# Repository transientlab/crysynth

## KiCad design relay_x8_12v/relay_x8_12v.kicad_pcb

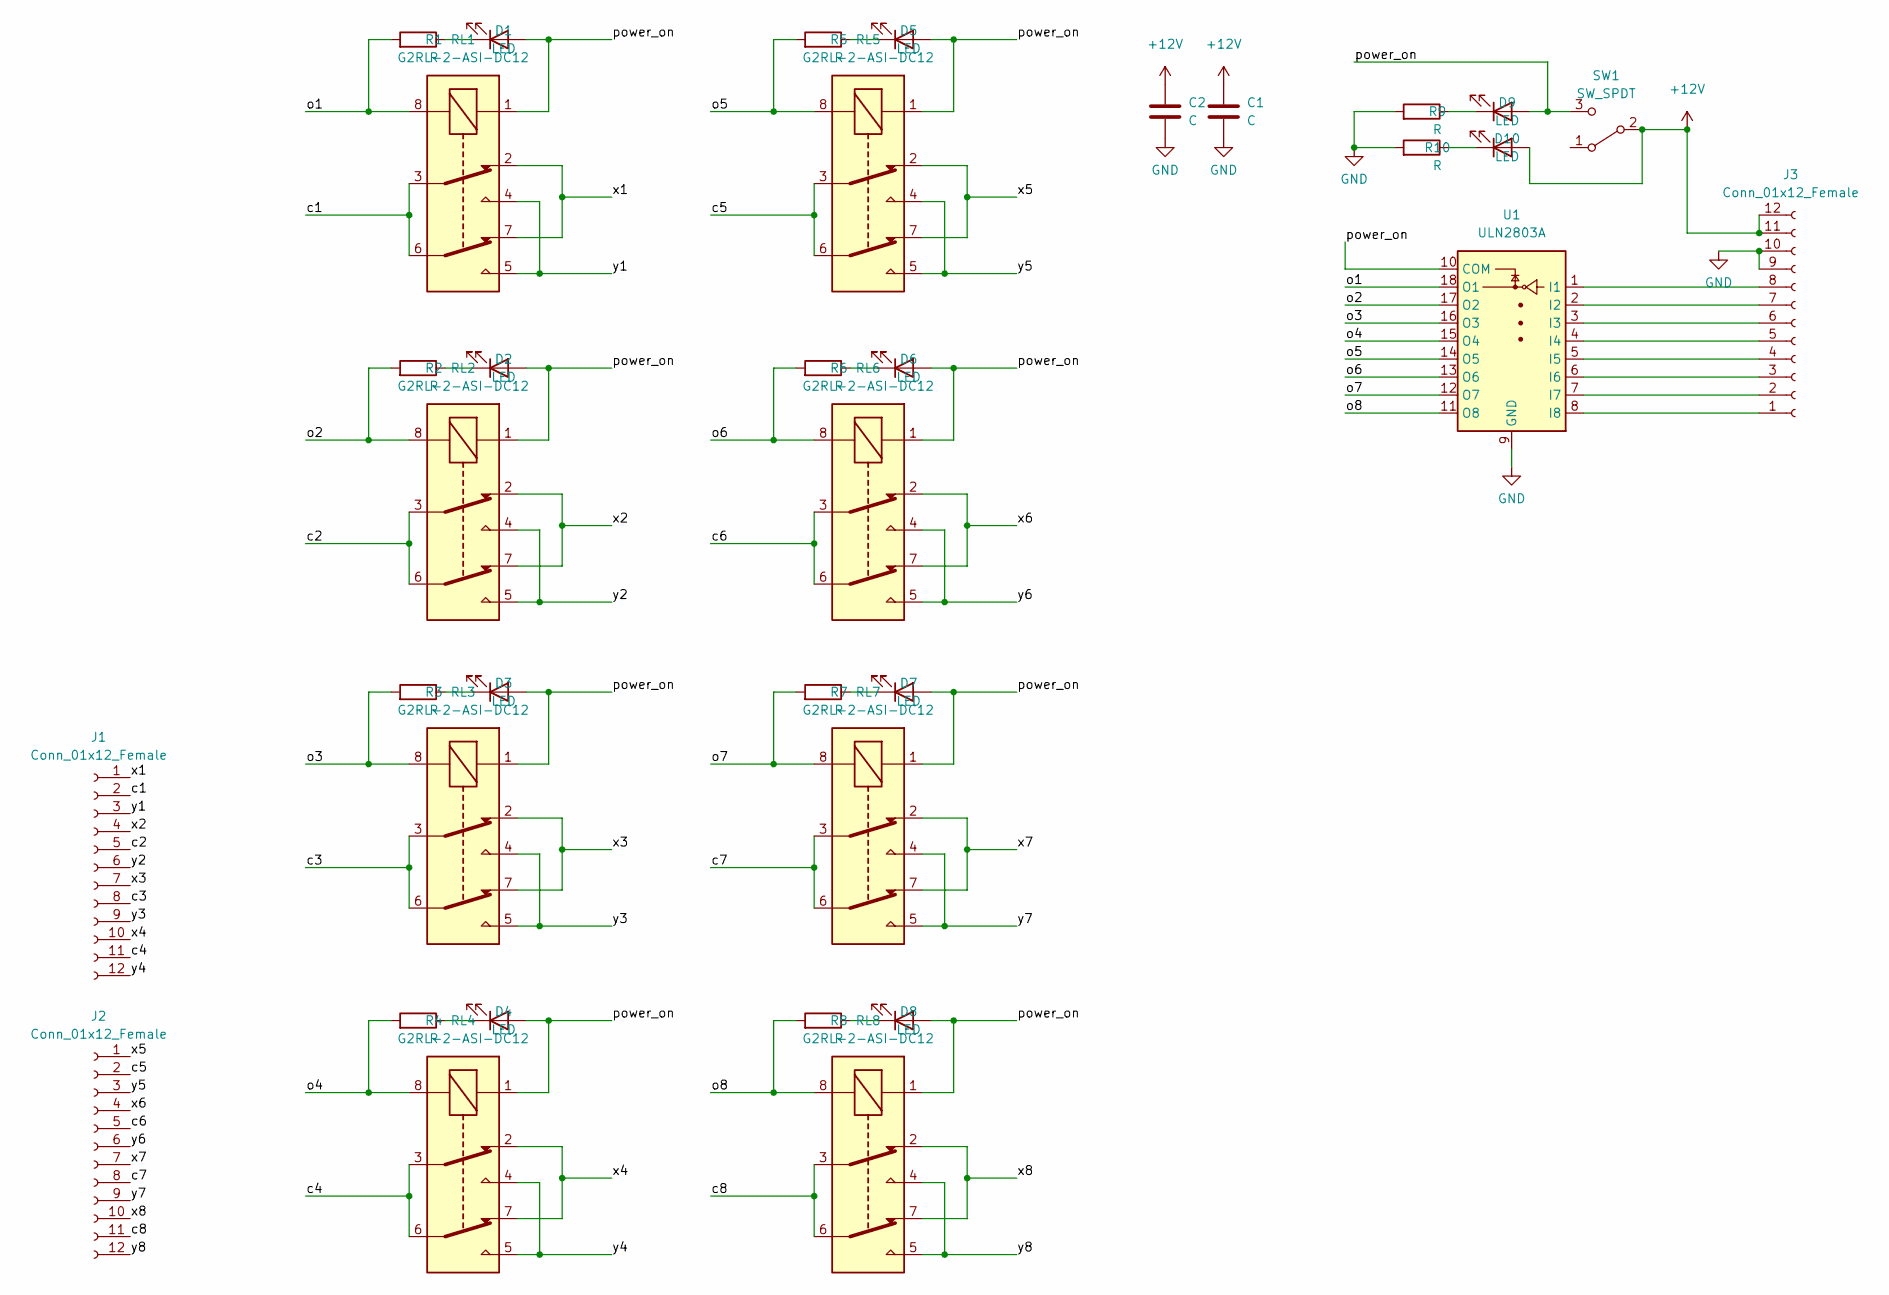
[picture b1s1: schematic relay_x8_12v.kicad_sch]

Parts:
C1, C2: C; C_Radial_D6.3mm_H11.0mm_P2.50mm
D1, D2, D3, D4, D5, D6, D7, D8, D9, D10: LED; LED_Rectangular_W5.0mm_H2.0mm
J1, J2, J3: Conn_01x12_Female; conn_large_12
R1, R2, R3, R4, R5, R6, R7, R8, R9, R10: R; R_Axial_DIN0207_L6.3mm_D2.5mm_P7.62mm_Horizontal
RL1, RL2, RL3, RL4, RL5, RL6, RL7, RL8: G2RL-2-ASI-DC12; Relay_DPDT_Omron_G2RL
SW1: SW_SPDT; sw_spdt_large
U1: ULN2803A; DIP-18_W7.62mm_Socket_LongPads

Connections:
+12V: C1.1, C2.1, D10.2 (A), J3.11, J3.12, SW1.2 (B)
/c1: J1.2, RL1.3, RL1.6
/c2: J1.5, RL2.3, RL2.6
/c3: J1.8, RL3.3, RL3.6
/c4: J1.11, RL4.3, RL4.6
/c5: J2.2, RL5.3, RL5.6
/c6: J2.5, RL6.3, RL6.6
/c7: J2.8, RL7.3, RL7.6
/c8: J2.11, RL8.3, RL8.6
/o1: R1.2, RL1.8, U1.18 (O1)
/o2: R2.2, RL2.8, U1.17 (O2)
/o3: R3.2, RL3.8, U1.16 (O3)
/o4: R4.2, RL4.8, U1.15 (O4)
/o5: R5.2, RL5.8, U1.14 (O5)
/o6: R6.2, RL6.8, U1.13 (O6)
/o7: R7.2, RL7.8, U1.12 (O7)
/o8: R8.2, RL8.8, U1.11 (O8)
/power_on: D1.2 (A), D2.2 (A), D3.2 (A), D4.2 (A), D5.2 (A), D6.2 (A), D7.2 (A), D8.2 (A), D9.2 (A), RL1.1, RL2.1, RL3.1, RL4.1, RL5.1, RL6.1, RL7.1, RL8.1, SW1.3 (C), U1.10 (COM)
/x1: J1.1, RL1.2, RL1.7
/x2: J1.4, RL2.2, RL2.7
/x3: J1.7, RL3.2, RL3.7
/x4: J1.10, RL4.2, RL4.7
/x5: J2.1, RL5.2, RL5.7
/x6: J2.4, RL6.2, RL6.7
/x7: J2.7, RL7.2, RL7.7
/x8: J2.10, RL8.2, RL8.7
/y1: J1.3, RL1.4, RL1.5
/y2: J1.6, RL2.4, RL2.5
/y3: J1.9, RL3.4, RL3.5
/y4: J1.12, RL4.4, RL4.5
/y5: J2.3, RL5.4, RL5.5
/y6: J2.6, RL6.4, RL6.5
/y7: J2.9, RL7.4, RL7.5
/y8: J2.12, RL8.4, RL8.5
GND: C1.2, C2.2, J3.9, J3.10, R9.2, R10.2, U1.9 (GND)
unnamed: D1.1 (K), R1.1
unnamed: D2.1 (K), R2.1
unnamed: D3.1 (K), R3.1
unnamed: D4.1 (K), R4.1
unnamed: D5.1 (K), R5.1
unnamed: D6.1 (K), R6.1
unnamed: D7.1 (K), R7.1
unnamed: D8.1 (K), R8.1
unnamed: D9.1 (K), R9.1
unnamed: D10.1 (K), R10.1
unnamed: J3.1, U1.8 (I8)
unnamed: J3.2, U1.7 (I7)
unnamed: J3.3, U1.6 (I6)
unnamed: J3.4, U1.5 (I5)
unnamed: J3.5, U1.4 (I4)
unnamed: J3.6, U1.3 (I3)
unnamed: J3.7, U1.2 (I2)
unnamed: J3.8, U1.1 (I1)

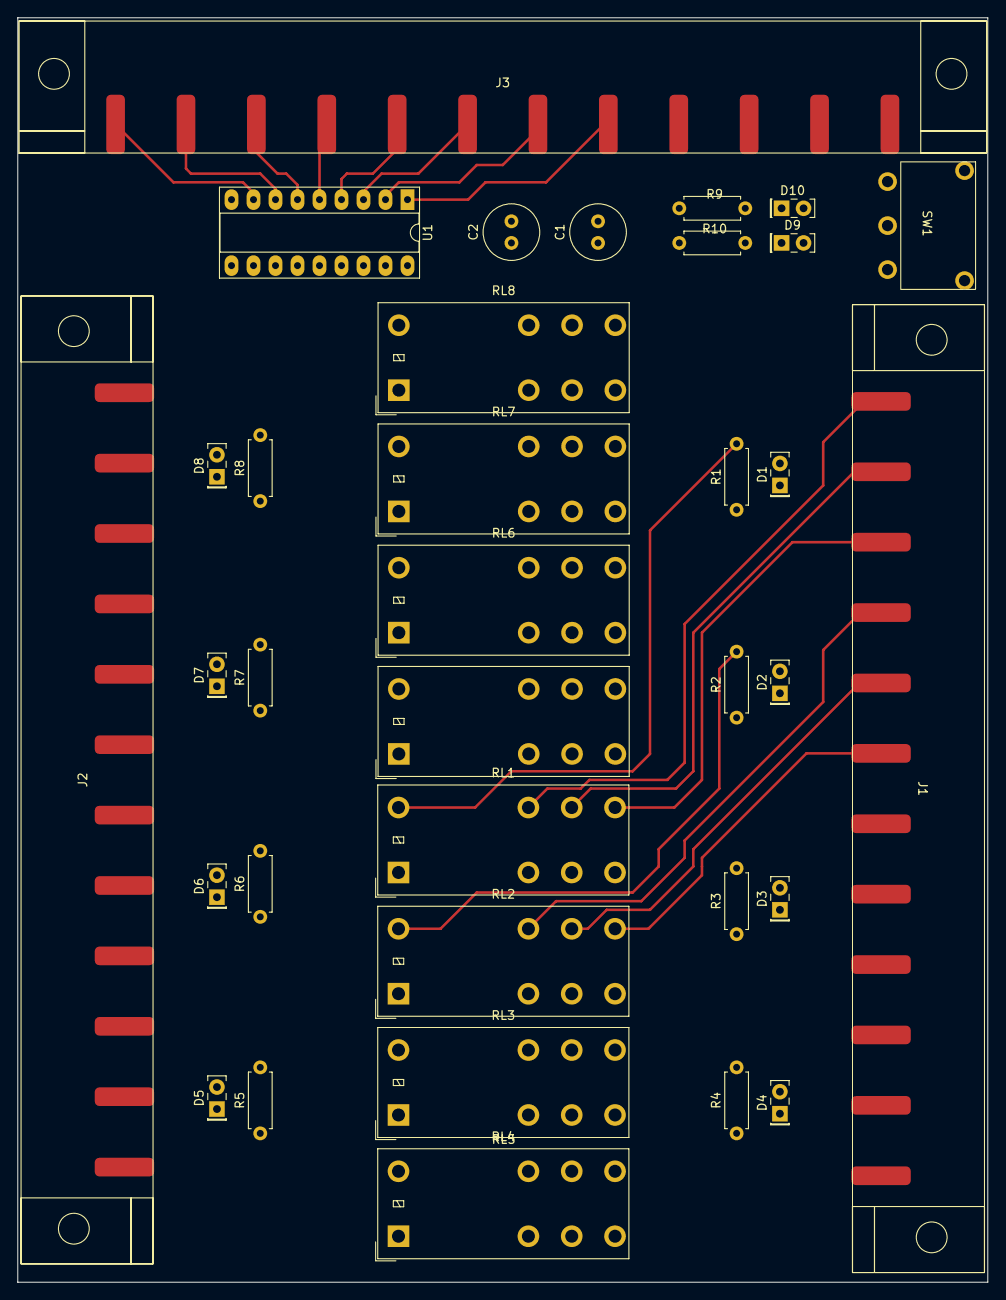
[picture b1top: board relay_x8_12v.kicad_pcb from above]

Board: 2 copper layers, 112.0 x 146.0 mm, 35 parts (0 on the bottom side), 53 nets.

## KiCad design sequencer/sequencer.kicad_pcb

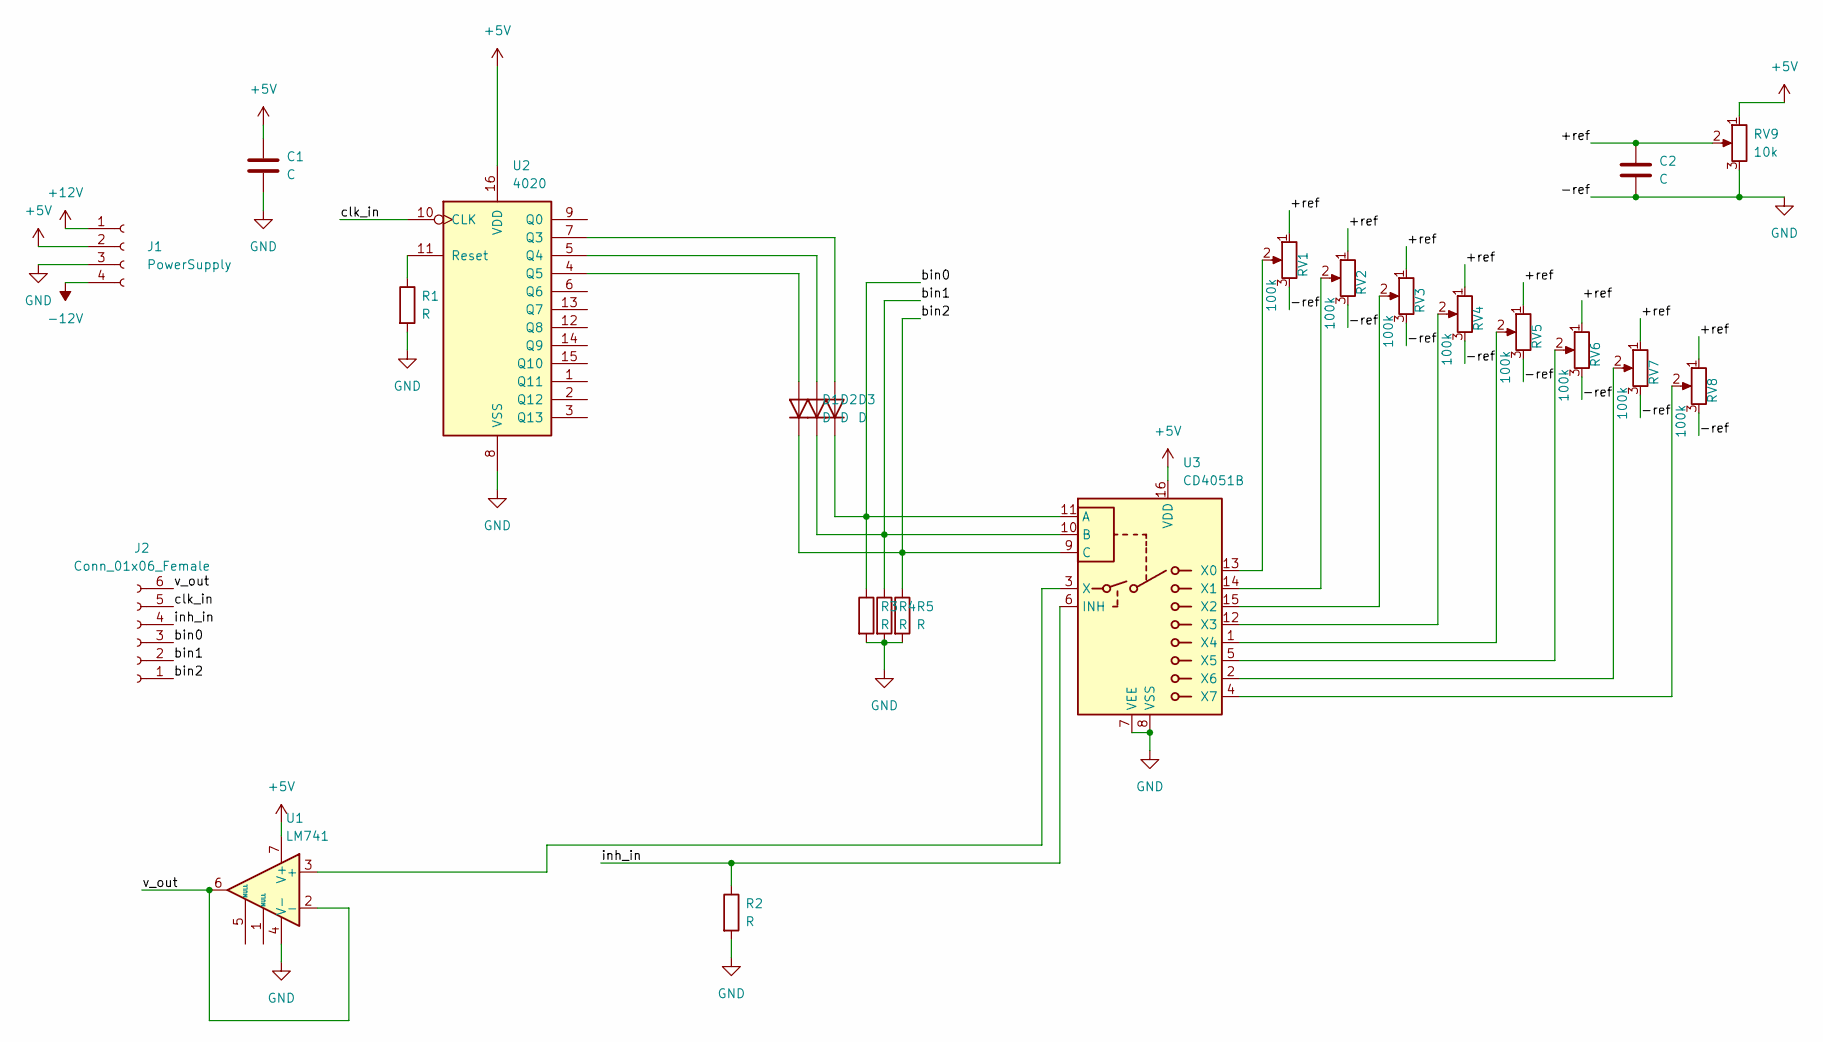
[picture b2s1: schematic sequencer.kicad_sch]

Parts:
C1, C2: C; C_Radial_D6.3mm_H11.0mm_P2.50mm
D1, D2, D3: D; D_T-1_P10.16mm_Horizontal
J1: PowerSupply; PinSocket_1x04_P1.27mm_Vertical
J2: Conn_01x06_Female; PinSocket_1x06_P2.54mm_Horizontal
R1, R2, R3, R4, R5: R; R_Axial_DIN0207_L6.3mm_D2.5mm_P7.62mm_Horizontal
RV1, RV2, RV3, RV4, RV5, RV6, RV7, RV8: 100k; Potentiometer_Alps_RK163_Single_Horizontal
RV9: 10k; Potentiometer_Alps_RK163_Single_Horizontal
U1: LM741; DIP-8_W7.62mm_Socket_LongPads
U2: 4020; DIP-16_W10.16mm_LongPads
U3: CD4051B; DIP-16_W7.62mm_Socket_LongPads

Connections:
+5V: C1.1, J1.2, RV9.1, U1.7 (V+), U2.16 (VDD), U3.16 (VDD)
+12V: J1.1
-12V: J1.4
/+ref: C2.1, RV1.1, RV2.1, RV3.1, RV4.1, RV5.1, RV6.1, RV7.1, RV8.1, RV9.2
/bin0: D3.1 (K), J2.3, R3.1, U3.11 (A)
/bin1: D2.1 (K), J2.2, R4.1, U3.10 (B)
/bin2: D1.1 (K), J2.1, R5.1, U3.9 (C)
/clk_in: J2.5, U2.10 (CLK)
/inh_in: J2.4, R2.1, U3.6 (INH)
/v_out: J2.6, U1.2 (-), U1.6
GND: C1.2, C2.2, J1.3, R1.2, R2.2, R3.2, R4.2, R5.2, RV1.3, RV2.3, RV3.3, RV4.3, RV5.3, RV6.3, RV7.3, RV8.3, RV9.3, U1.4 (V-), U2.8 (VSS), U3.7 (VEE), U3.8 (VSS)
unnamed: R1.1, U2.11 (Reset)
unnamed: RV1.2, U3.13 (X0)
unnamed: RV2.2, U3.14 (X1)
unnamed: RV3.2, U3.15 (X2)
unnamed: RV4.2, U3.12 (X3)
unnamed: RV5.2, U3.1 (X4)
unnamed: RV6.2, U3.5 (X5)
unnamed: RV7.2, U3.2 (X6)
unnamed: RV8.2, U3.4 (X7)
unnamed: U1.3 (+), U3.3 (X)
unnamed: D1.2 (A), U2.4 (Q5)
unnamed: D2.2 (A), U2.5 (Q4)
unnamed: D3.2 (A), U2.7 (Q3)

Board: 2 copper layers, 24 parts (0 on the bottom side), 22 nets, no tracks yet.

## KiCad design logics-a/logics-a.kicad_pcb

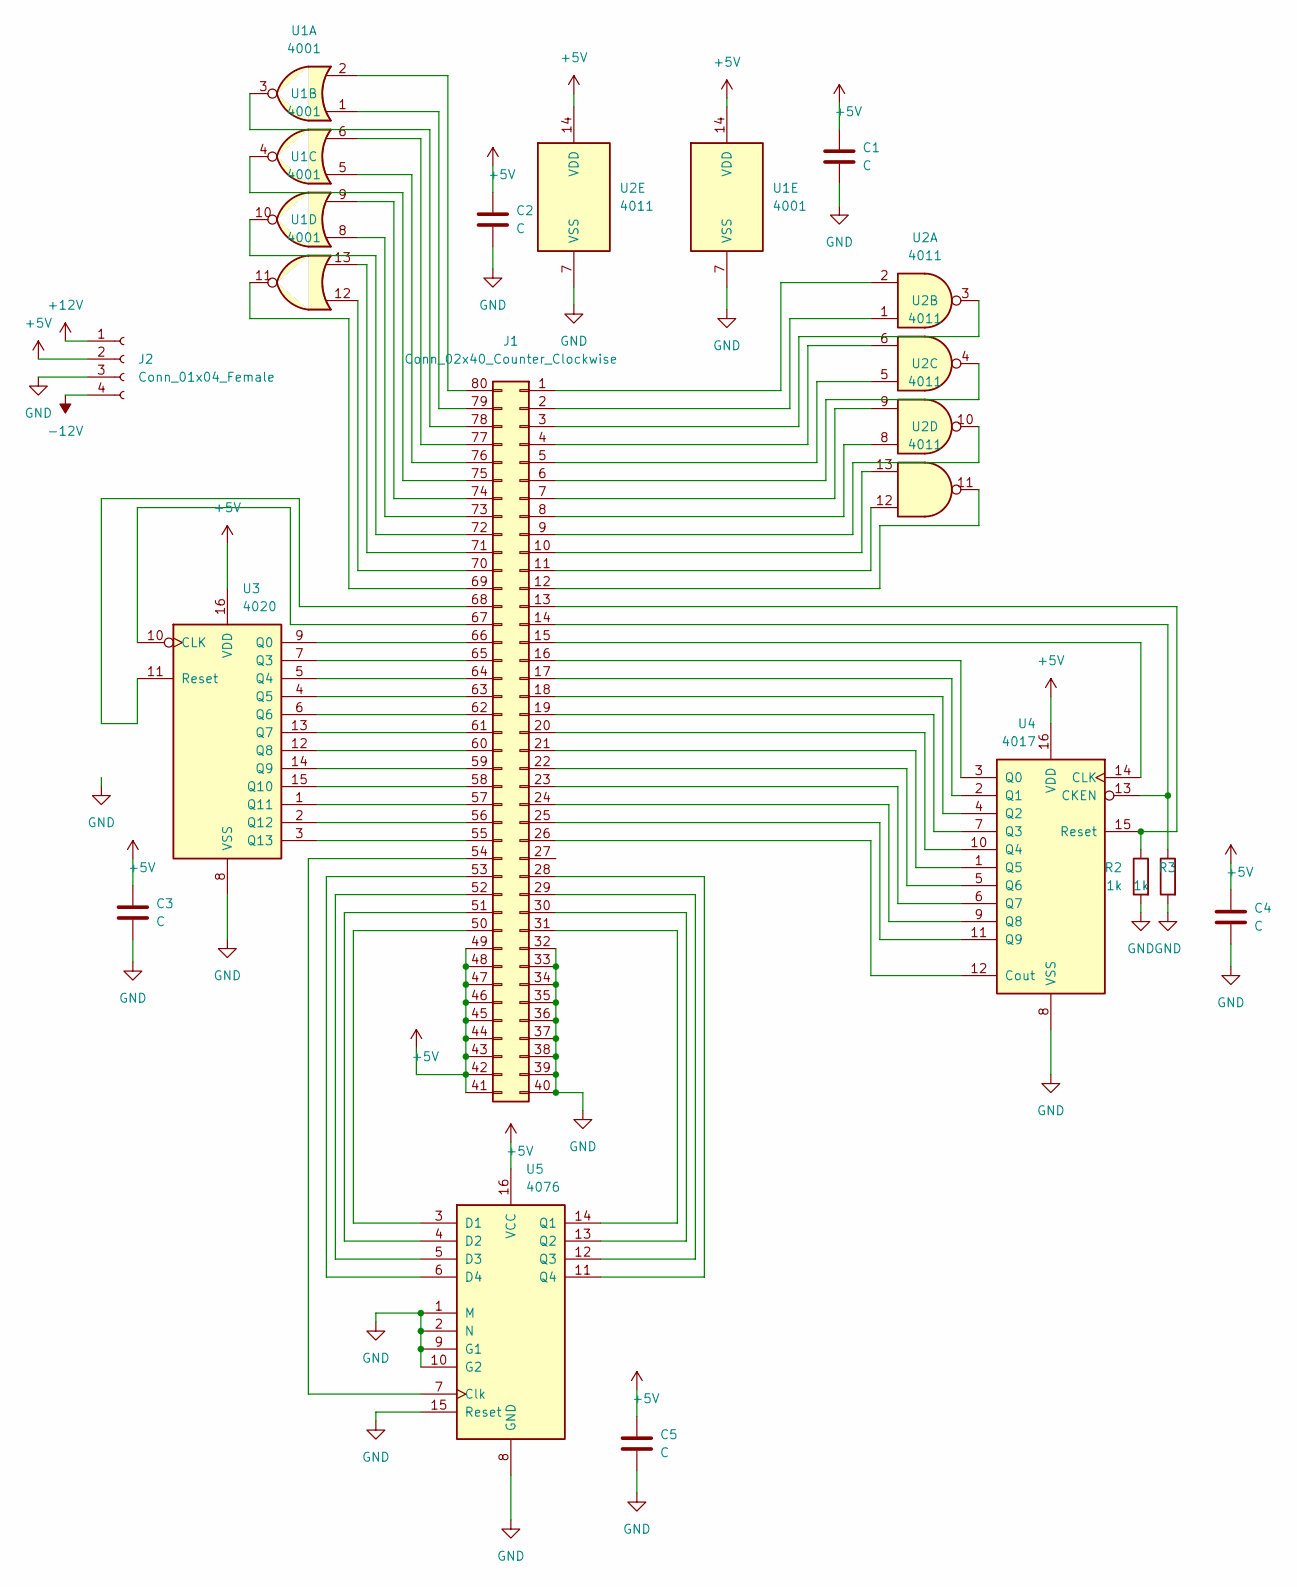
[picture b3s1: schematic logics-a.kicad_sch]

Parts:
C1, C2, C3, C4, C5: C; C_Radial_D6.3mm_H5.0mm_P2.50mm
J1: Conn_02x40_Counter_Clockwise; PinHeader_2x40_P2.54mm_Horizontal
J2: Conn_01x04_Female; PinSocket_1x04_P1.27mm_Vertical
R2, R3: 1k; R_Axial_DIN0204_L3.6mm_D1.6mm_P5.08mm_Horizontal
U1: 4001; DIP-14_W7.62mm_Socket_LongPads
U2: 4011; DIP-14_W7.62mm_Socket_LongPads
U3: 4020; DIP-16_W7.62mm_Socket_LongPads
U4: 4017; DIP-16_W7.62mm_Socket_LongPads
U5: 4076; DIP-16_W7.62mm_Socket_LongPads

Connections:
+5V: C1.1, C2.1, C3.1, C4.1, C5.1, J1.41, J1.42, J1.43, J1.44, J1.45, J1.46, J1.47, J1.48, J1.49, J2.2, U1.14 (VDD), U2.14 (VDD), U3.16 (VDD), U4.16 (VDD), U5.16 (VCC)
+12V: J2.1
-12V: J2.4
GND: C1.2, C2.2, C3.2, C4.2, C5.2, J1.32, J1.33, J1.34, J1.35, J1.36, J1.37, J1.38, J1.39, J1.40, J2.3, R2.2, R3.2, U1.7 (VSS), U2.7 (VSS), U3.8 (VSS), U4.8 (VSS), U5.1 (M), U5.2 (N), U5.8 (GND), U5.9 (G1), U5.10 (G2), U5.15 (Reset)
unnamed: J1.1, U2.2
unnamed: J1.2, U2.1
unnamed: J1.3, U2.3
unnamed: J1.4, U2.6
unnamed: J1.5, U2.5
unnamed: J1.6, U2.4
unnamed: J1.7, U2.9
unnamed: J1.8, U2.8
unnamed: J1.9, U2.10
unnamed: J1.10, U2.13
unnamed: J1.11, U2.12
unnamed: J1.12, U2.11
unnamed: J1.64, U3.5 (Q4)
unnamed: J1.66, U3.9 (Q0)
unnamed: J1.67, U3.10 (CLK)
unnamed: J1.70, U1.12
unnamed: J1.71, U1.13
unnamed: J1.72, U1.10
unnamed: J1.73, U1.8
unnamed: J1.74, U1.9
unnamed: J1.75, U1.4
unnamed: J1.76, U1.5
unnamed: J1.77, U1.6
unnamed: J1.78, U1.3
unnamed: J1.79, U1.1
unnamed: J1.80, U1.2
unnamed: J1.13, R2.1, U4.15 (Reset)
unnamed: J1.14, R3.1, U4.13 (CKEN)
unnamed: J1.69, U1.11
unnamed: J1.57, U3.1 (Q11)
unnamed: J1.56, U3.2 (Q12)
unnamed: J1.55, U3.3 (Q13)
unnamed: J1.63, U3.4 (Q5)
unnamed: J1.62, U3.6 (Q6)
unnamed: J1.65, U3.7 (Q3)
unnamed: J1.68, U3.11 (Reset)
unnamed: J1.60, U3.12 (Q8)
unnamed: J1.61, U3.13 (Q7)
unnamed: J1.59, U3.14 (Q9)
unnamed: J1.58, U3.15 (Q10)
unnamed: J1.21, U4.1 (Q5)
unnamed: J1.17, U4.2 (Q1)
unnamed: J1.16, U4.3 (Q0)
unnamed: J1.18, U4.4 (Q2)
unnamed: J1.22, U4.5 (Q6)
unnamed: J1.23, U4.6 (Q7)
unnamed: J1.19, U4.7 (Q3)
unnamed: J1.24, U4.9 (Q8)
unnamed: J1.20, U4.10 (Q4)
unnamed: J1.25, U4.11 (Q9)
unnamed: J1.26, U4.12 (Cout)
unnamed: J1.15, U4.14 (CLK)
unnamed: J1.50, U5.3 (D1)
unnamed: J1.51, U5.4 (D2)
unnamed: J1.52, U5.5 (D3)
unnamed: J1.53, U5.6 (D4)
unnamed: J1.54, U5.7 (Clk)
unnamed: J1.28, U5.11 (Q4)
unnamed: J1.29, U5.12 (Q3)
unnamed: J1.30, U5.13 (Q2)
unnamed: J1.31, U5.14 (Q1)

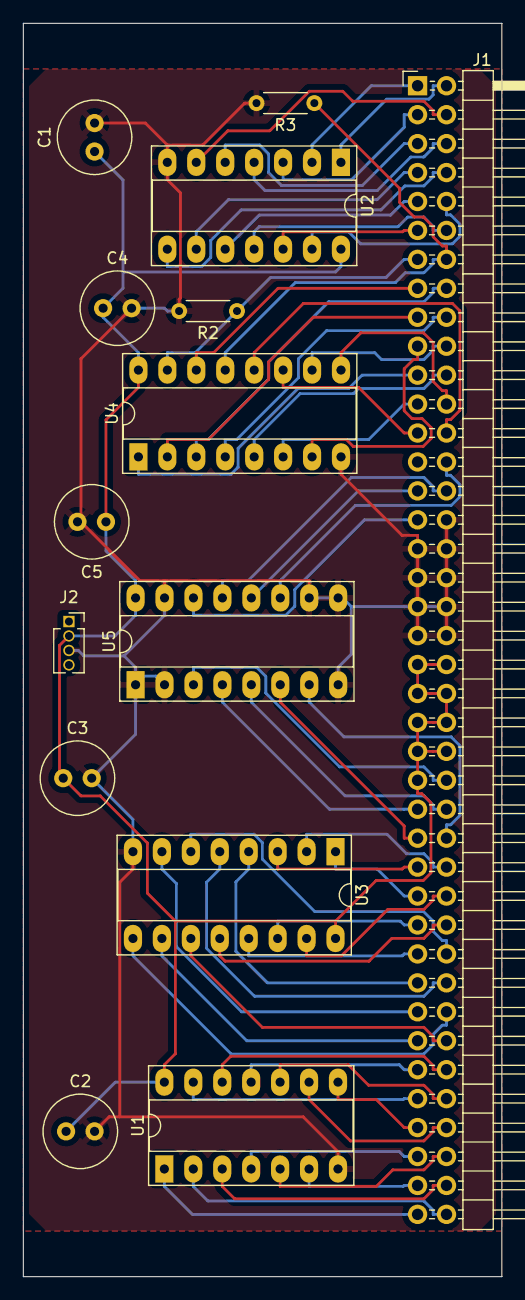
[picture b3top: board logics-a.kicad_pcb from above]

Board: 2 copper layers, 42.0 x 110.0 mm, 14 parts (0 on the bottom side), 63 nets.

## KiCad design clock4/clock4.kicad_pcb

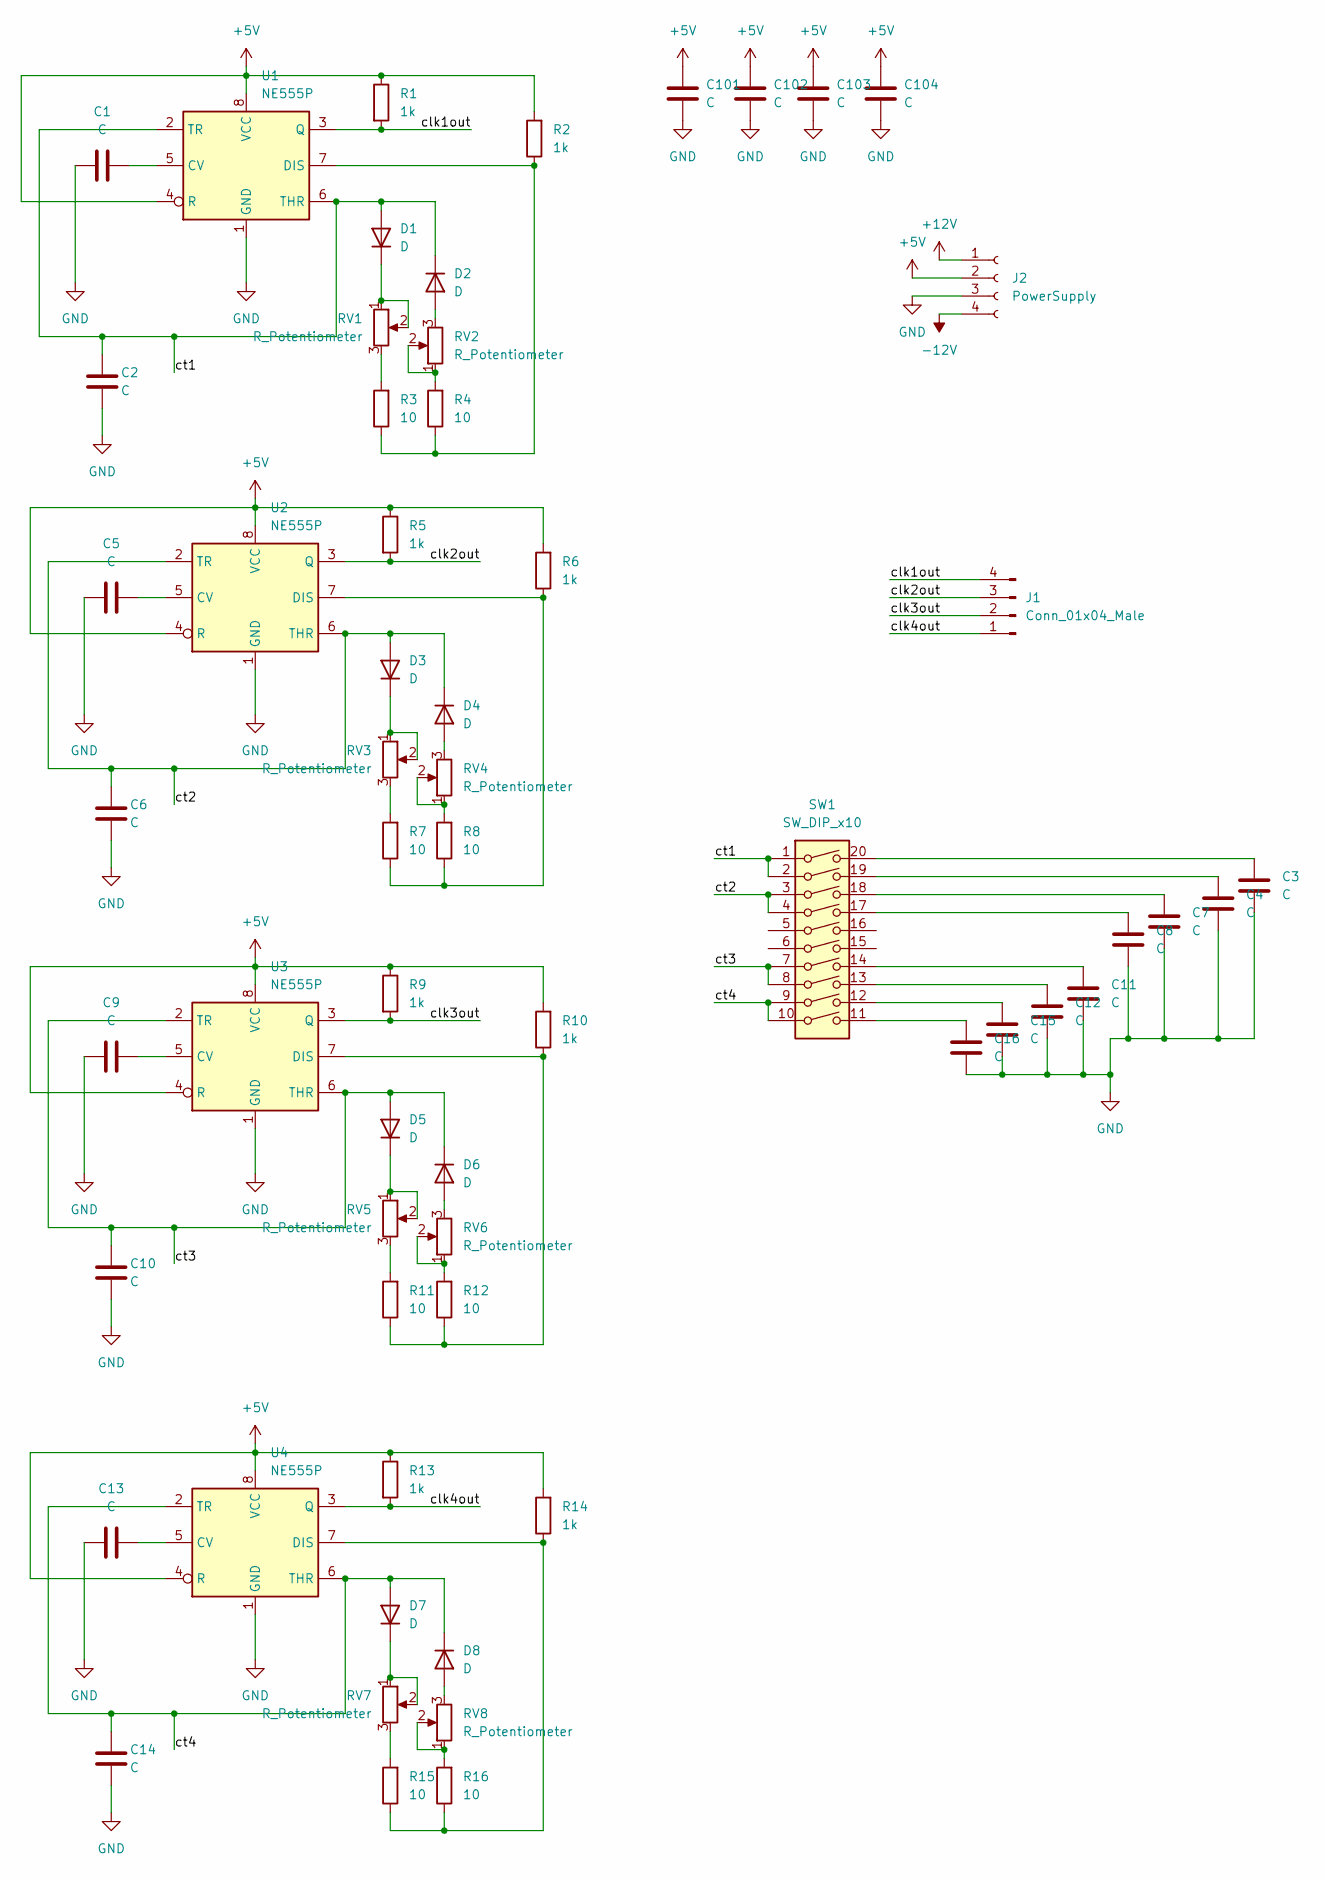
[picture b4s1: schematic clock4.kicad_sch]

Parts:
C1, C2, C4, C5, C6, C8, C9, C10, C12, C13, C14, C16, C101, C102, C103, C104: C; C_Disc_D5.0mm_W2.5mm_P2.50mm
C3, C7, C11, C15: C; C_Radial_D6.3mm_H11.0mm_P2.50mm
D1, D2, D3, D4, D5, D6, D7, D8: D; D_A-405_P5.08mm_Vertical_AnodeUp
J1: Conn_01x04_Male; PinHeader_1x04_P2.54mm_Horizontal
J2: PowerSupply; PinHeader_1x04_P1.27mm_Vertical
R1, R2, R5, R6, R9, R10, R13, R14: 1k; R_Axial_DIN0204_L3.6mm_D1.6mm_P5.08mm_Horizontal
R3, R4, R7, R8, R11, R12, R15, R16: 10; R_Axial_DIN0204_L3.6mm_D1.6mm_P5.08mm_Horizontal
RV1, RV2, RV3, RV4, RV5, RV6, RV7, RV8: R_Potentiometer; Potentiometer_Piher_PT-6-H_Horizontal
SW1: SW_DIP_x10; SW_DIP_SPSTx10_Piano_10.8x26.96mm_W7.62mm_P2.54mm
U1, U2, U3, U4: NE555P; DIP-8_W7.62mm

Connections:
+5V: C101.1, C102.1, C103.1, C104.1, J2.2, R1.1, R2.2, R5.1, R6.2, R9.1, R10.2, R13.1, R14.2, U1.4 (R), U1.8 (VCC), U2.4 (R), U2.8 (VCC), U3.4 (R), U3.8 (VCC), U4.4 (R), U4.8 (VCC)
+12V: J2.1
-12V: J2.4
/clk1out: J1.4, R1.2, U1.3 (Q)
/clk2out: J1.3, R5.2, U2.3 (Q)
/clk3out: J1.2, R9.2, U3.3 (Q)
/clk4out: J1.1, R13.2, U4.3 (Q)
/ct1: C2.2, D1.2 (A), D2.1 (K), SW1.1, SW1.2, U1.2 (TR), U1.6 (THR)
/ct2: C6.2, D3.2 (A), D4.1 (K), SW1.3, SW1.4, U2.2 (TR), U2.6 (THR)
/ct3: C10.2, D5.2 (A), D6.1 (K), SW1.7, SW1.8, U3.2 (TR), U3.6 (THR)
/ct4: C14.2, D7.2 (A), D8.1 (K), SW1.9, SW1.10, U4.2 (TR), U4.6 (THR)
GND: C1.1, C2.1, C3.1, C4.1, C5.1, C6.1, C7.1, C8.1, C9.1, C10.1, C11.1, C12.1, C13.1, C14.1, C15.1, C16.1, C101.2, C102.2, C103.2, C104.2, J2.3, U1.1 (GND), U2.1 (GND), U3.1 (GND), U4.1 (GND)
unnamed: C1.2, U1.5 (CV)
unnamed: C3.2, SW1.20
unnamed: C4.2, SW1.19
unnamed: C5.2, U2.5 (CV)
unnamed: C7.2, SW1.18
unnamed: C8.2, SW1.17
unnamed: C9.2, U3.5 (CV)
unnamed: C11.2, SW1.14
unnamed: C12.2, SW1.13
unnamed: C13.2, U4.5 (CV)
unnamed: C15.2, SW1.12
unnamed: C16.2, SW1.11
unnamed: D1.1 (K), RV1.1, RV1.2
unnamed: D2.2 (A), RV2.3
unnamed: D3.1 (K), RV3.1, RV3.2
unnamed: D4.2 (A), RV4.3
unnamed: D5.1 (K), RV5.1, RV5.2
unnamed: D6.2 (A), RV6.3
unnamed: D7.1 (K), RV7.1, RV7.2
unnamed: D8.2 (A), RV8.3
unnamed: R2.1, R3.1, R4.1, U1.7 (DIS)
unnamed: R3.2, RV1.3
unnamed: R4.2, RV2.1, RV2.2
unnamed: R6.1, R7.1, R8.1, U2.7 (DIS)
unnamed: R7.2, RV3.3
unnamed: R8.2, RV4.1, RV4.2
unnamed: R10.1, R11.1, R12.1, U3.7 (DIS)
unnamed: R11.2, RV5.3
unnamed: R12.2, RV6.1, RV6.2
unnamed: R14.1, R15.1, R16.1, U4.7 (DIS)
unnamed: R15.2, RV7.3
unnamed: R16.2, RV8.1, RV8.2

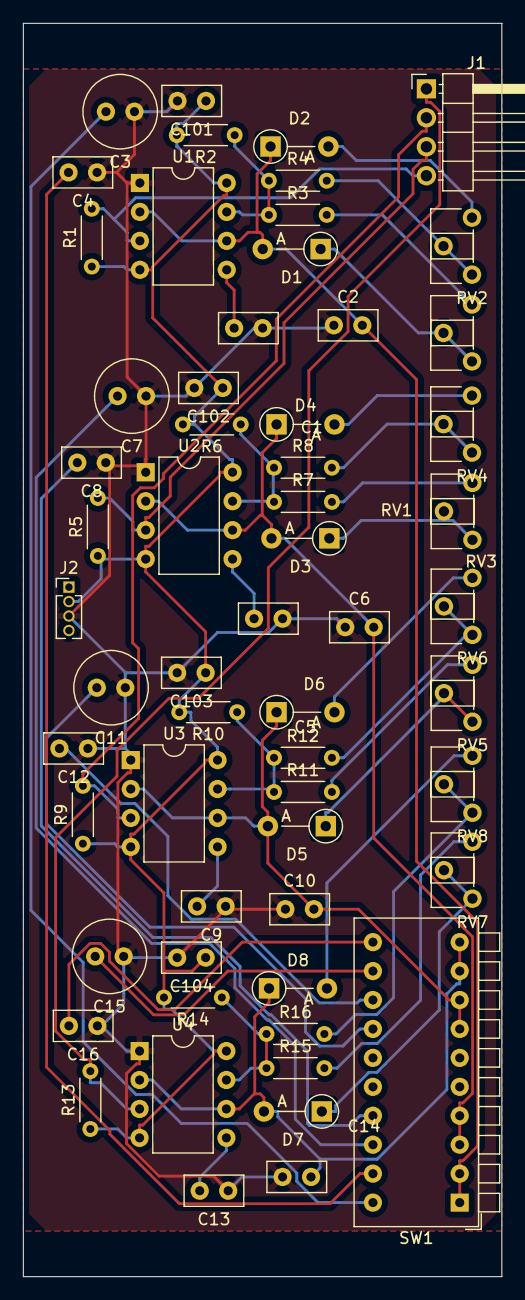
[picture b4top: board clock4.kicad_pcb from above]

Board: 2 copper layers, 42.0 x 110.0 mm, 59 parts (0 on the bottom side), 42 nets.

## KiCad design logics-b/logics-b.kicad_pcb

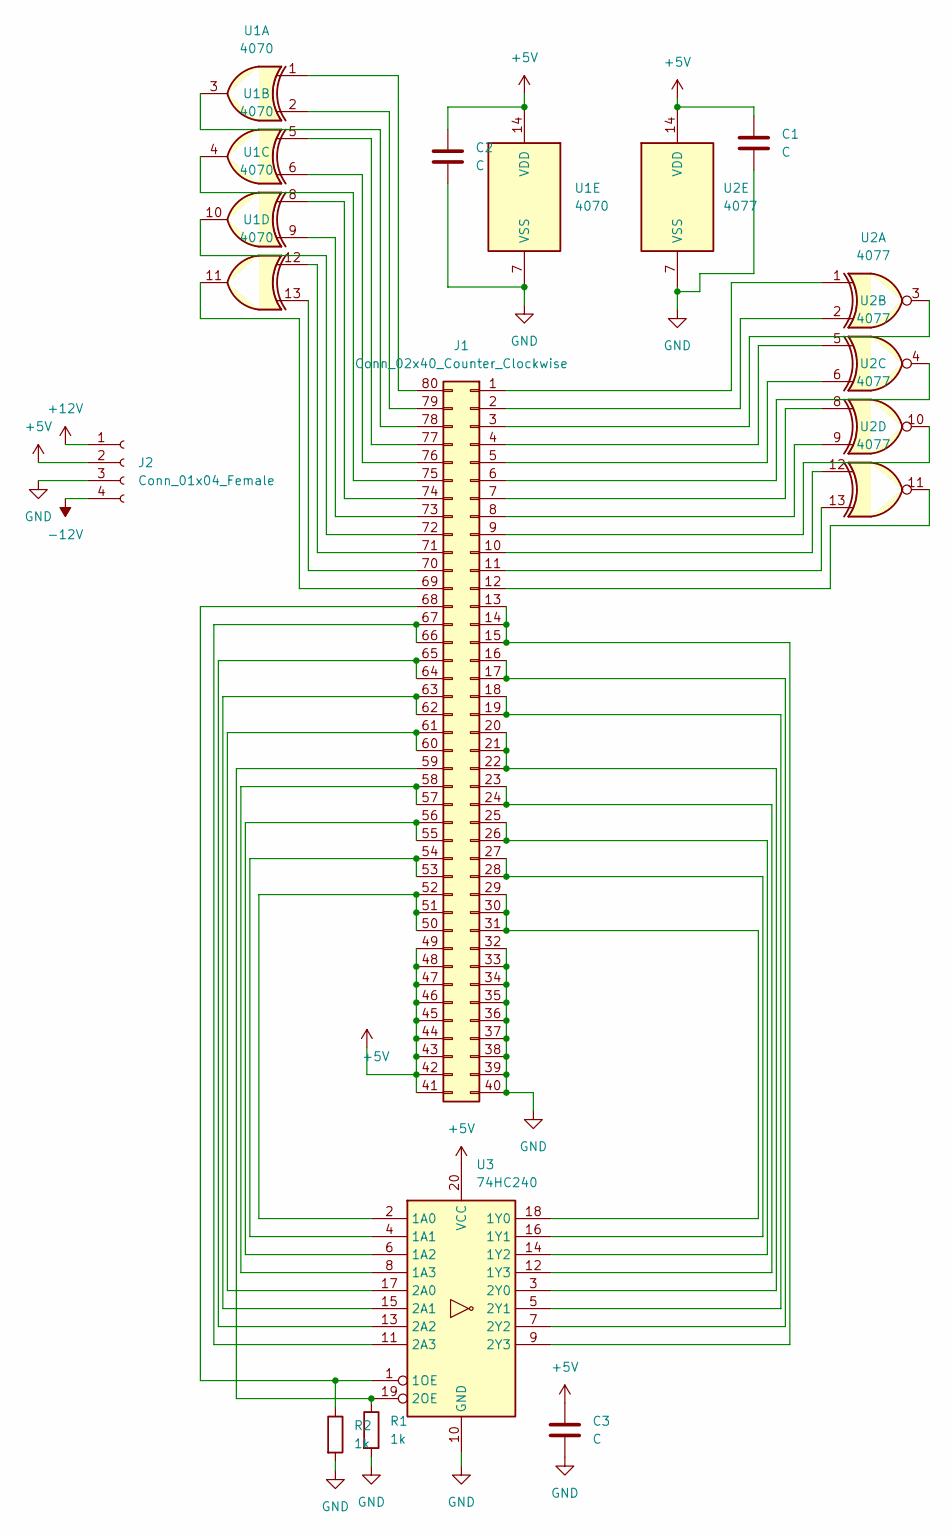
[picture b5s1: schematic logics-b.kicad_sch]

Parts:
C1, C2, C3: C; C_Radial_D6.3mm_H7.0mm_P2.50mm
J1: Conn_02x40_Counter_Clockwise; PinHeader_2x40_P2.54mm_Horizontal
J2: Conn_01x04_Female; PinSocket_1x04_P1.27mm_Vertical
R1, R2: 1k; R_Axial_DIN0204_L3.6mm_D1.6mm_P5.08mm_Horizontal
U1: 4070; DIP-14_W10.16mm_LongPads
U2: 4077; DIP-14_W10.16mm_LongPads
U3: 74HC240; DIP-20_W7.62mm_Socket_LongPads

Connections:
+5V: C1.1, C2.1, C3.1, J1.41, J1.42, J1.43, J1.44, J1.45, J1.46, J1.47, J1.48, J1.49, J2.2, U1.14 (VDD), U2.14 (VDD), U3.20 (VCC)
+12V: J2.1
-12V: J2.4
GND: C1.2, C2.2, C3.2, J1.32, J1.33, J1.34, J1.35, J1.36, J1.37, J1.38, J1.39, J1.40, J2.3, R1.2, R2.2, U1.7 (VSS), U2.7 (VSS), U3.10 (GND)
unnamed: J1.1, U2.1
unnamed: J1.2, U2.2
unnamed: J1.3, U2.3
unnamed: J1.4, U2.5
unnamed: J1.5, U2.6
unnamed: J1.6, U2.4
unnamed: J1.7, U2.8
unnamed: J1.8, U2.9
unnamed: J1.9, U2.10
unnamed: J1.10, U2.12
unnamed: J1.11, U2.13
unnamed: J1.12, U2.11
unnamed: J1.20, J1.21, J1.22, U3.3 (2Y0)
unnamed: J1.23, J1.24, U3.12 (1Y3)
unnamed: J1.25, J1.26, U3.14 (1Y2)
unnamed: J1.27, J1.28, U3.16 (1Y1)
unnamed: J1.29, J1.30, J1.31, U3.18 (1Y0)
unnamed: J1.69, U1.11
unnamed: J1.72, U1.10
unnamed: J1.77, U1.5
unnamed: J1.79, U1.2
unnamed: J1.80, U1.1
unnamed: J1.59, R1.1, U3.19 (2OE)
unnamed: J1.68, R2.1, U3.1 (1OE)
unnamed: J1.78, U1.3
unnamed: J1.75, U1.4
unnamed: J1.76, U1.6
unnamed: J1.74, U1.8
unnamed: J1.73, U1.9
unnamed: J1.71, U1.12
unnamed: J1.70, U1.13
unnamed: J1.50, J1.51, J1.52, U3.2 (1A0)
unnamed: J1.53, J1.54, U3.4 (1A1)
unnamed: J1.18, J1.19, U3.5 (2Y1)
unnamed: J1.55, J1.56, U3.6 (1A2)
unnamed: J1.16, J1.17, U3.7 (2Y2)
unnamed: J1.57, J1.58, U3.8 (1A3)
unnamed: J1.13, J1.14, J1.15, U3.9 (2Y3)
unnamed: J1.66, J1.67, U3.11 (2A3)
unnamed: J1.64, J1.65, U3.13 (2A2)
unnamed: J1.62, J1.63, U3.15 (2A1)
unnamed: J1.60, J1.61, U3.17 (2A0)

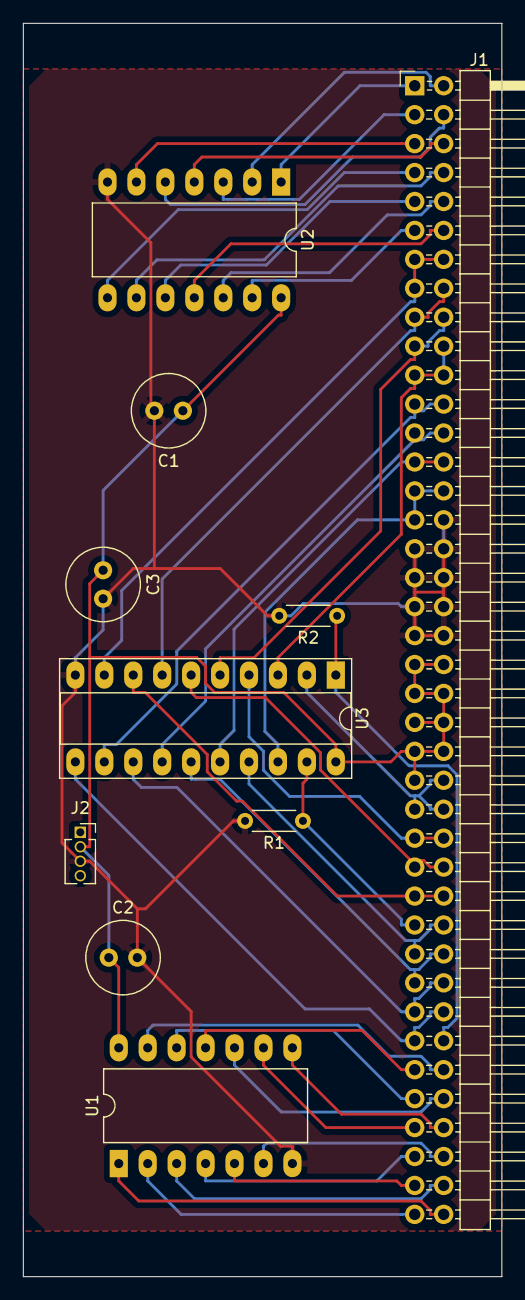
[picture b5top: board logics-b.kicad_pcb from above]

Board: 2 copper layers, 42.0 x 110.0 mm, 10 parts (0 on the bottom side), 44 nets.
